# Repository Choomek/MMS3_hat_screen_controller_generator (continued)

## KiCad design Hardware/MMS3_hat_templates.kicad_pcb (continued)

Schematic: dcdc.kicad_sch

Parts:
C1307, C1324: 100uF; CP_Elec_10x10; MPN VZH101M1KTR-1010; LCSC C249838
C1308, C1309, C1310, C1311, C1312, C1313: 10uF; C_0805; Voltage Rated 50V; Tolerance ±10%; Part GRM21BR61H106KE43L; LCSC C440198
C1314, C1315: 220nF; C_0805; Voltage Rated 50V; Tolerance ±10%; Part CL21B224KBFNNNE; LCSC C5378
C1316: 4.7nF; C_0402; Voltage Rated 50V; Tolerance ±10%; Part 0402B472K500NT; LCSC C1538
C1317: 47pF; C_0402; Voltage Rated 50V; Tolerance ±5%; Part 0402CG470J500NT; LCSC C1567
C1318: 100nF; C_0805; Voltage Rated 100V; Tolerance ±10%; Part CL21B104KCFNNNE; LCSC C28233
C1319, C1320, C1321, C1322, C1323: 22uF; C_0805; Voltage Rated 25V; Tolerance ±20%; Part CL21A226MAQNNNE; LCSC C45783
D1301: SMF58CA; D_SOD-123FL; Clamping Voltage 93.6V; Voltage - Breakdown 71.2V; Part SMF58CA; LCSC C42371753
D1302, D1303: SS510B; D_SMB; Forward Voltage (Vf@If) 0.85V@5.0A; Reverse Voltage (Vr) 100V; Part SS510B; LCSC C7420368
L1302: YSPI1050-100M; L_Sunlord_MWSA1005S; LCSC C497897
R1304, R1305: 24.9kΩ; R_0402; Overload Voltage (Max) 50V; Tolerance ±1%; Part 0402WGF2402TCE; LCSC C25874
R1306: 12kΩ; R_0402; Overload Voltage (Max) 50V; Tolerance ±1%; Part 0402WGF1202TCE; LCSC C25752
R1307: 240kΩ; R_0603; Overload Voltage (Max) 75V; Tolerance ±1%; Part 0603WAF2403T5E; LCSC C4197
R1308: 43kΩ; R_0603; Overload Voltage (Max) 75V; Tolerance ±1%; Part 0603WAF4302T5E; LCSC C23172
R1309: 8.2kΩ; R_0402; Overload Voltage (Max) 50V; Tolerance ±1%; Part 0402WGF8201TCE; LCSC C25924
TP1301, TP1302, TP1303, TP1304, TP1305: TestPoint; TestPoint_Pad_D1.0mm
U1302: TPS54560BDDA; Texas_R-PDSO-G8_EP2.95x4.9mm_Mask2.4x3.1mm_ThermalVias

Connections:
/User Area/24V to 5V low current DC-DC power converter/Cap_protec: C1308.2, C1309.1, C1310.2, C1311.1, C1312.2, C1313.1, C1314.2, C1315.1, R1304.2, R1305.1
/User Area/VIN_BRD: C1307.1, C1308.1, C1310.1, C1312.1, C1314.1, D1301.1, R1304.1, TP1301.1 (1_1), U1302.2 (VIN), U1302.3 (EN)
GND: C1307.2, C1309.2, C1311.2, C1313.2, C1315.2, C1316.2, C1317.2, C1319.2, C1320.2, C1321.2, C1322.2, C1323.2, C1324.2, D1301.2, D1302.2, R1305.2, R1307.2, R1309.2, U1302.7 (GND), U1302.9 (GND); also elsewhere on the board
unnamed: C1316.1, R1306.2
unnamed: C1319.1, C1320.1, C1321.1, C1322.1, C1323.1, D1303.2, L1302.2, R1308.1, TP1304.1 (1_1)
unnamed: C1318.2, U1302.1 (BOOT)
unnamed: C1317.1, R1306.1, TP1302.1 (1_1), U1302.6 (COMP)
unnamed: R1308.2, R1309.1, TP1305.1 (1_1), U1302.5 (FB)
unnamed: R1307.1, TP1303.1 (1_1), U1302.4 (RT/CLK)
unnamed: C1318.1, D1302.1, L1302.1, U1302.8 (SW)
VCC: C1324.1, D1303.1; also elsewhere on the board

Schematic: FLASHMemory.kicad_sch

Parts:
C1001: 100nF; C_0402; Voltage Rated 50V; Tolerance ±10%; Part CL05B104KB54PNC; LCSC C307331
R1001: 10kΩ; R_0603; Overload Voltage (Max) 75V; Tolerance ±1%; Part 0603WAF1002T5E; LCSC C25804
U1001: W25Q128JVS; SOIC-8_5.3x5.3mm_P1.27mm

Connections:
+3V3: C1001.1, R1001.1, U1001.8 (VCC); also elsewhere on the board
/User Area/FLASH Memory/MCU_QSPI.IO0: U1001.5 (DI/IO_{0}); also elsewhere on the board
/User Area/FLASH Memory/MCU_QSPI.IO1: U1001.2 (DO/IO_{1}); also elsewhere on the board
/User Area/FLASH Memory/MCU_QSPI.IO2: U1001.3 (~WP/IO_{2}); also elsewhere on the board
/User Area/FLASH Memory/MCU_QSPI.IO3: U1001.7 (~HOLD/~RESET/IO_{3}); also elsewhere on the board
/User Area/FLASH Memory/MCU_QSPI.SCLK: U1001.6 (CLK); also elsewhere on the board
/User Area/FLASH Memory/QSPI_CS_FLASH: R1001.2, U1001.1 (~CS); also elsewhere on the board
GND: C1001.2, U1001.4 (GND); also elsewhere on the board

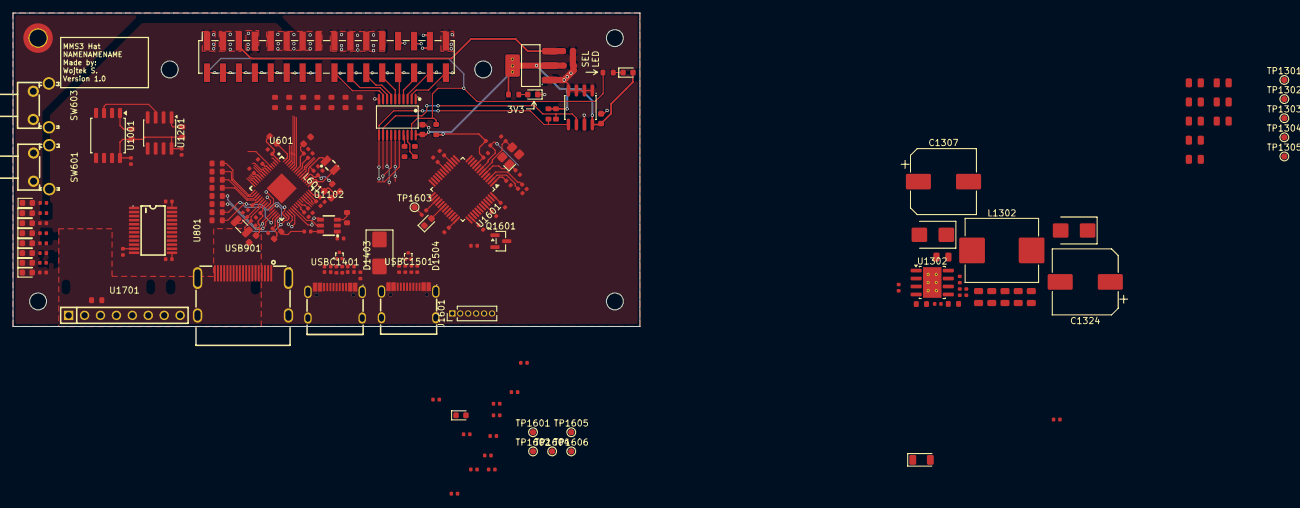
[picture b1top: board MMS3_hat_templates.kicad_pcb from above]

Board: 2 copper layers, 100.0 x 50.0 mm, 187 parts (1 on the bottom side), 136 nets.

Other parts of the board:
C301, C501: 100nF; C_0603
D301: Red; D_0603
J201: Chainbus in; PinHeader_2x16_P2.54mm_Vertical_SMD
J202: Chainbus Out; PinSocket_2x16_P2.54mm_Vertical_SMD
R301, R302, R303, R304, R305, R306, R307, R308, R309, R310: 10kΩ; R_0603
R311: 1kΩ; R_0603
R312, R313: 0Ω; R_0603
U302: SN74CB3Q3245PWR; C470961_TSSOP-20_L6_5-W4_4-P0_65-LS6_4-BL
U501: M24C64; SOIC-8_L5.0-W4.0-P1.27-LS6.0-BL

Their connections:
+3V3: C301.1, C501.1, D301.2, R301.1, R302.1, R304.1, R305.1, R306.1, R308.1, R310.1, U302.20 (VCC), U501.8 (VCC); also elsewhere on the board
+5V: J201.3, J201.5, J202.3, J202.5; also elsewhere on the board
+12V stby: J201.29, J202.29
/Bus_switch/Chainbus.CS: R301.2, U302.13 (B6); also elsewhere on the board
/Bus_switch/Chainbus.MISO: R307.1, U302.16 (B3); also elsewhere on the board
/Bus_switch/Chainbus.MOSI: R309.1, U302.15 (B4); also elsewhere on the board
/Bus_switch/Chainbus.RX: R306.2, R312.2
/Bus_switch/Chainbus.SCK: R302.2, R303.1, U302.14 (B5); also elsewhere on the board
/Bus_switch/Chainbus.SCL: R304.2, U302.12 (B7), U501.6 (SCL); also elsewhere on the board
/Bus_switch/Chainbus.SDA: R308.2, U302.11 (B8), U501.5 (SDA); also elsewhere on the board
/Bus_switch/Chainbus.TX: R305.2, R313.2
/Bus_switch/Chainbus_In.CS: J201.22, J202.22, U302.7 (A6)
/Bus_switch/Chainbus_In.MISO: J201.28, J202.28, U302.4 (A3)
/Bus_switch/Chainbus_In.MOSI: J201.26, J202.26, U302.5 (A4)
/Bus_switch/Chainbus_In.RX: J201.32, J202.32, U302.2 (A1)
/Bus_switch/Chainbus_In.SCK: J201.24, J202.24, U302.6 (A5)
/Bus_switch/Chainbus_In.SCL: J201.20, J202.20, U302.8 (A7)
/Bus_switch/Chainbus_In.SDA: J201.18, J202.18, U302.9 (A8)
/Bus_switch/Chainbus_In.TX: J201.30, J202.30, U302.3 (A2)
/Bus_switch/Poka_Yoke_RX: R312.1, U302.18 (B1)
/Bus_switch/Poka_Yoke_TX: R313.1, U302.17 (B2)
/Bus_switch/SEL1: J201.2, R310.2, R311.1, U302.19 (OE#)
/Interboard_connector/Pin_25: J201.25, J202.25
/Interboard_connector/Pin_27: J201.27, J202.27
/Interboard_connector/SEL2: J201.4, J202.2
/Interboard_connector/SEL3: J201.6, J202.4
/Interboard_connector/SEL4: J201.8, J202.6
/Interboard_connector/SEL5: J201.10, J202.8
/Interboard_connector/SEL6: J201.12, J202.10
/Interboard_connector/SEL7: J201.14, J202.12
/Interboard_connector/SEL8: J201.16, J202.14
GND: C301.2, C501.2, J201.1, J201.7, J201.17, J201.19, J201.21, J201.23, J201.31, J202.1, J202.7, J202.17, J202.19, J202.21, J202.23, J202.31, R303.2, R307.2, R309.2, U302.10 (GND), U501.1 (A0), U501.2 (A1), U501.3 (A2), U501.4 (VSS), U501.7 (#WC); also elsewhere on the board
unnamed: D301.1, R311.2
VIN_CHAINBUS: J201.9, J201.11, J201.13, J201.15, J202.9, J202.11, J202.13, J202.15
